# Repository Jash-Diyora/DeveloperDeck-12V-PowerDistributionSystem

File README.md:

# DeveloperDeck-12V--PowerDistributionSystem

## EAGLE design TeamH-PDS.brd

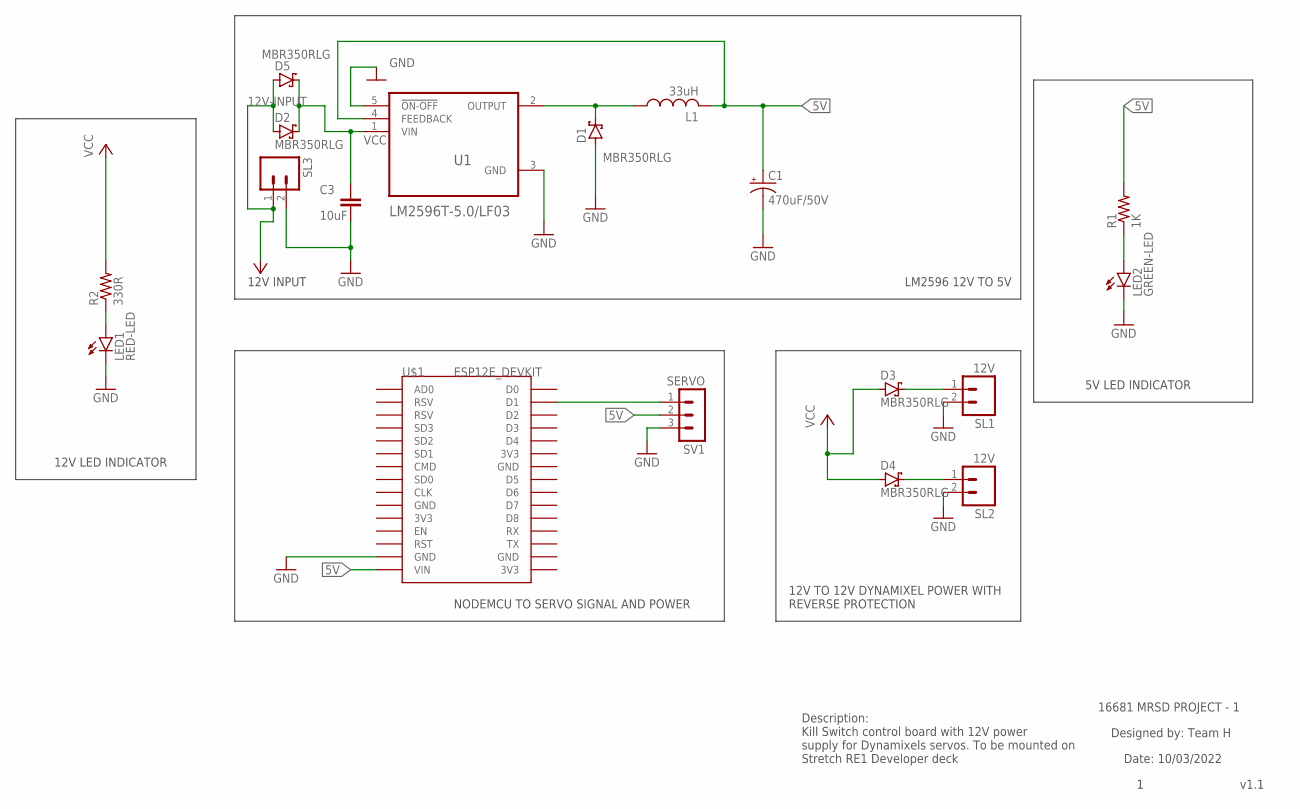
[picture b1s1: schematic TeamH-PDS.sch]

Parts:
C1: 470uF/50V; E2-5
C3: 10uF; C2.5-3
D1, D2, D3, D4, D5: MBR350RLG; C4111-15
L1: 33uH; 0207/7
LED1: RED-LED; LED5MM
LED2: GREEN-LED; LED5MM
R1: 1K; 0204/5
R2: 330R; 0204/5
SL1, SL2: 12V; 02P
SL3: 12V-INPUT; 02P
SV1: SERVO; MA03-1
U1: LM2596T-5.0/LF03; TO170P1016X470X2092-5
U$1: ESP12E_DEVKIT

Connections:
5V: C1.+, L1.2, R1.2, SV1.2, U1.4 (FEEDBACK), U$1.VIN
GND: C1.-, C3.2, D1.A, LED1.K (C), LED2.K (C), SL1.2, SL2.2, SL3.2, SV1.3, U1.3 (GND), U1.5 (!ON-OFF), U$1.GND@1 (GND)
unnamed: SV1.1, U$1.D1
unnamed: D1.C, L1.1, U1.2 (OUTPUT)
unnamed: LED1.A, R2.1
unnamed: D3.C, SL1.1
unnamed: D4.C, SL2.1
unnamed: C3.1, D2.C, D5.C, U1.1 (VIN)
unnamed: LED2.A, R1.1
VCC: D2.A, D3.A, D4.A, D5.A, R2.2, SL3.1

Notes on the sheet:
LM2596 12V TO 5V
NODEMCU TO SERVO SIGNAL AND POWER
12V TO 12V DYNAMIXEL POWER WITH REVERSE PROTECTION
Designed by: Team H
Description: Kill Switch control board with 12V power supply for Dynamixels servos. To be mounted on Stretch RE1 Developer deck
16681 MRSD PROJECT - 1
12V INPUT
5V LED INDICATOR
12V LED INDICATOR
v1.1
Date: 10/03/2022

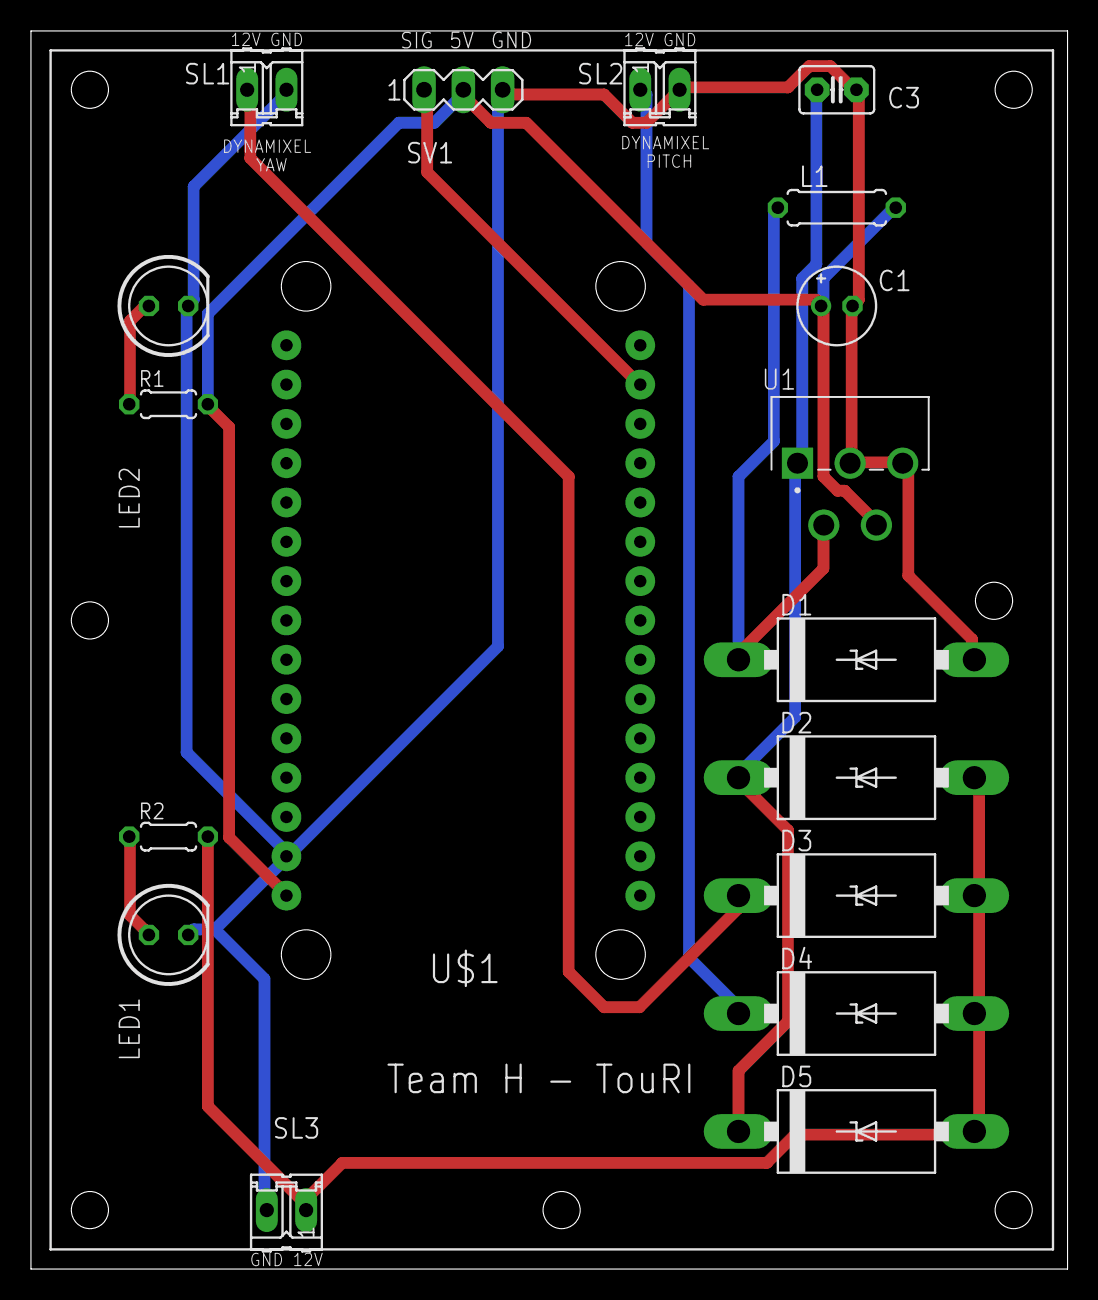
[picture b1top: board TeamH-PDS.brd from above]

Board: 2 copper layers, 67.0 x 80.0 mm, 18 parts (0 on the bottom side), 10 nets.

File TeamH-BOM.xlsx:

Qty | Value | Device | Package | Parts | Description | Purchase Link | Price (Per Piece) | Available in MRSD Inventory
3 | TERMINAL CONNECTOR | M02 | 02P | SL1, SL2, SL3 | Quick Connector | Link | 1.84 | No, Need to order
1 | 10uF/50V | C2,5-3 | C2.5-3 | C3 | Capacitor, American Symbol | Link | 0.6 | No, Need to order
1 | 330R | R-US_0204/5 | 0204/5 | R2 | Resistor, American Symbol | Link | 0.05 | Yes
1 | 33uH | L-US0207/7 | 0207/7 | L1 | Inductor, American Symbol | Link | 1.95 | Yes
1 | 470uF/50V | CPOL-USE2-5 | E2-5 | C1 | Polarized Capacitor, American Symbol | Link | 0.7 | No, Need to order
1 | 1K | R-US_0204/5 | 0204/5 | R1 | Resistor, American Symbol | Link | 0.06 | Yes
1 | ESP12E_DEVKIT | NODEMCU | NODEMCU | U$1 | ESP12E NodeMCU Microcontroller | Link | 5.33 | Yes
2 | LED | LED5MM | LED5MM | LED1, LED2 | LED | Link | 7.0000000000000007E-2 | Yes
1 | LM2596T-5.0/LF03 | LM2596T-5.0/LF03 | TO170P1016X470X2092-5 | U1 | DC-DC Converter | Link | 6.12 | No, Need to order
5 | MBR350RLG | 1N5908 | C4111-15 | D1, D2, D3, D4, D5 | Diode | Link | 0.56999999999999995 | No, Need to order
1 | SERVO | MA03-1 | MA03-1 | SV1 | Pin Header | Link | 2 | Yes
